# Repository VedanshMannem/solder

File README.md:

# solder

First time making PCBs & messing with circuits

I wanted to learn more about transistors and came across a pretty cool design on YouTube. I wanted to do something similar but also incorporate the motor disc, so I made a PCB with alternating lights and a button to turn on the motor. 

## BOM:
1. BatteryHolder_Keystone_3034_1x20mm	1
2. CP_Radial_D8.0mm_P5.00mm	2
3. LED_D5.0mm	2
4. PinHeader_1x02_P2.54mm_Vertical	1
5. TO-92L_HandSolder	2
6. R_Axial_DIN0207_L6.3mm_D2.5mm_P7.62mm_Horizontal 5
7. SW_PUSH_6mm	1

## Images

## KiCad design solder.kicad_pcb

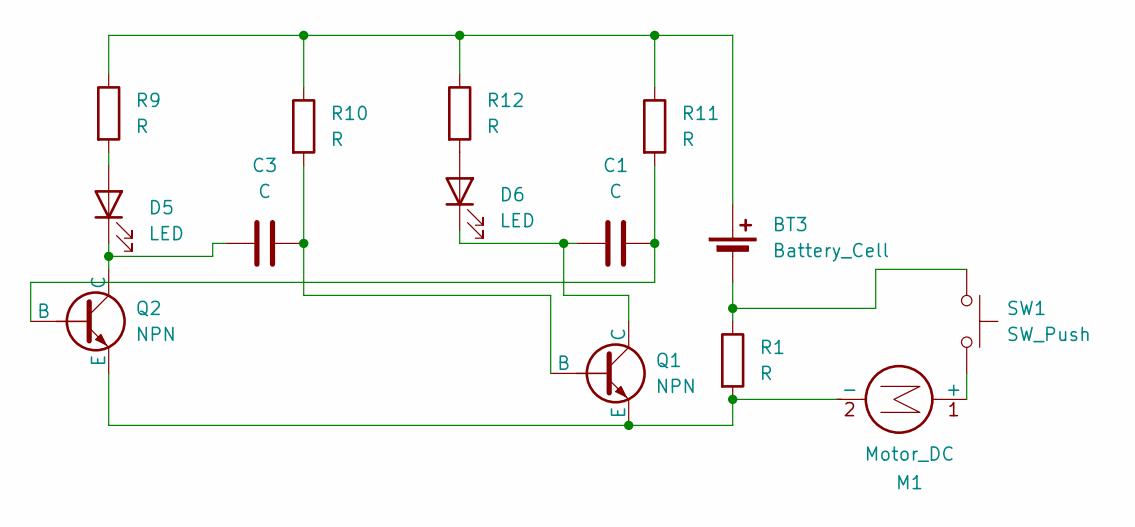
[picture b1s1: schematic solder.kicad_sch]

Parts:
BT3: Battery_Cell; BatteryHolder_Keystone_3034_1x20mm
C1, C3: C; CP_Radial_D8.0mm_P5.00mm
D5, D6: LED; LED_D5.0mm
M1: Motor_DC; PinHeader_1x02_P2.54mm_Vertical
Q1, Q2: NPN; TO-92L_HandSolder
R1, R9, R10, R11, R12: R; R_Axial_DIN0207_L6.3mm_D2.5mm_P7.62mm_Horizontal
SW1: SW_Push; SW_PUSH_6mm

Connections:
unnamed: BT3.1 (+), R9.1, R10.1, R11.1, R12.1
unnamed: BT3.2 (-), R1.1, SW1.1
unnamed: D5.2 (A), R9.2
unnamed: C3.1, D5.1 (K), Q2.1 (C)
unnamed: D6.2 (A), R12.2
unnamed: C1.1, D6.1 (K), Q1.1 (C)
unnamed: M1.1 (+), SW1.2
unnamed: M1.2 (-), Q1.3 (E), Q2.3 (E), R1.2
unnamed: C3.2, Q1.2 (B), R10.2
unnamed: C1.2, Q2.2 (B), R11.2

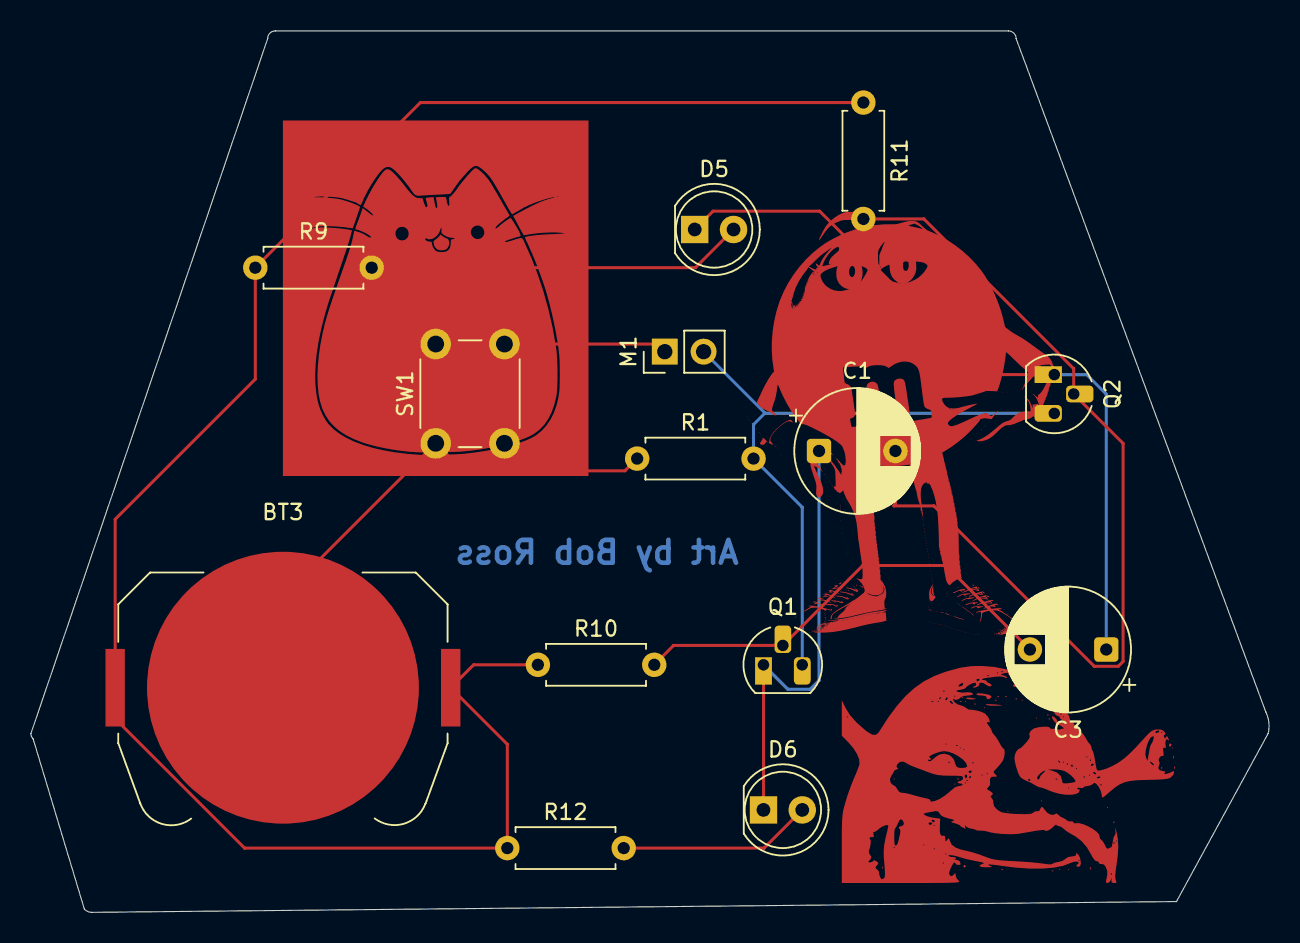
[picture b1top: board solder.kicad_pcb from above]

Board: 2 copper layers, 81.1 x 57.7 mm, 14 parts (0 on the bottom side), 10 nets.

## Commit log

2025-05-21 Adding PCB files
2025-05-21 Updated Fabrication Toolkit Output
    Changed the location of capacitor so that it allows the blinking
2025-05-21 Update README.md
    Change layer of images
2025-05-21 Update README.md
    updated PCB images
